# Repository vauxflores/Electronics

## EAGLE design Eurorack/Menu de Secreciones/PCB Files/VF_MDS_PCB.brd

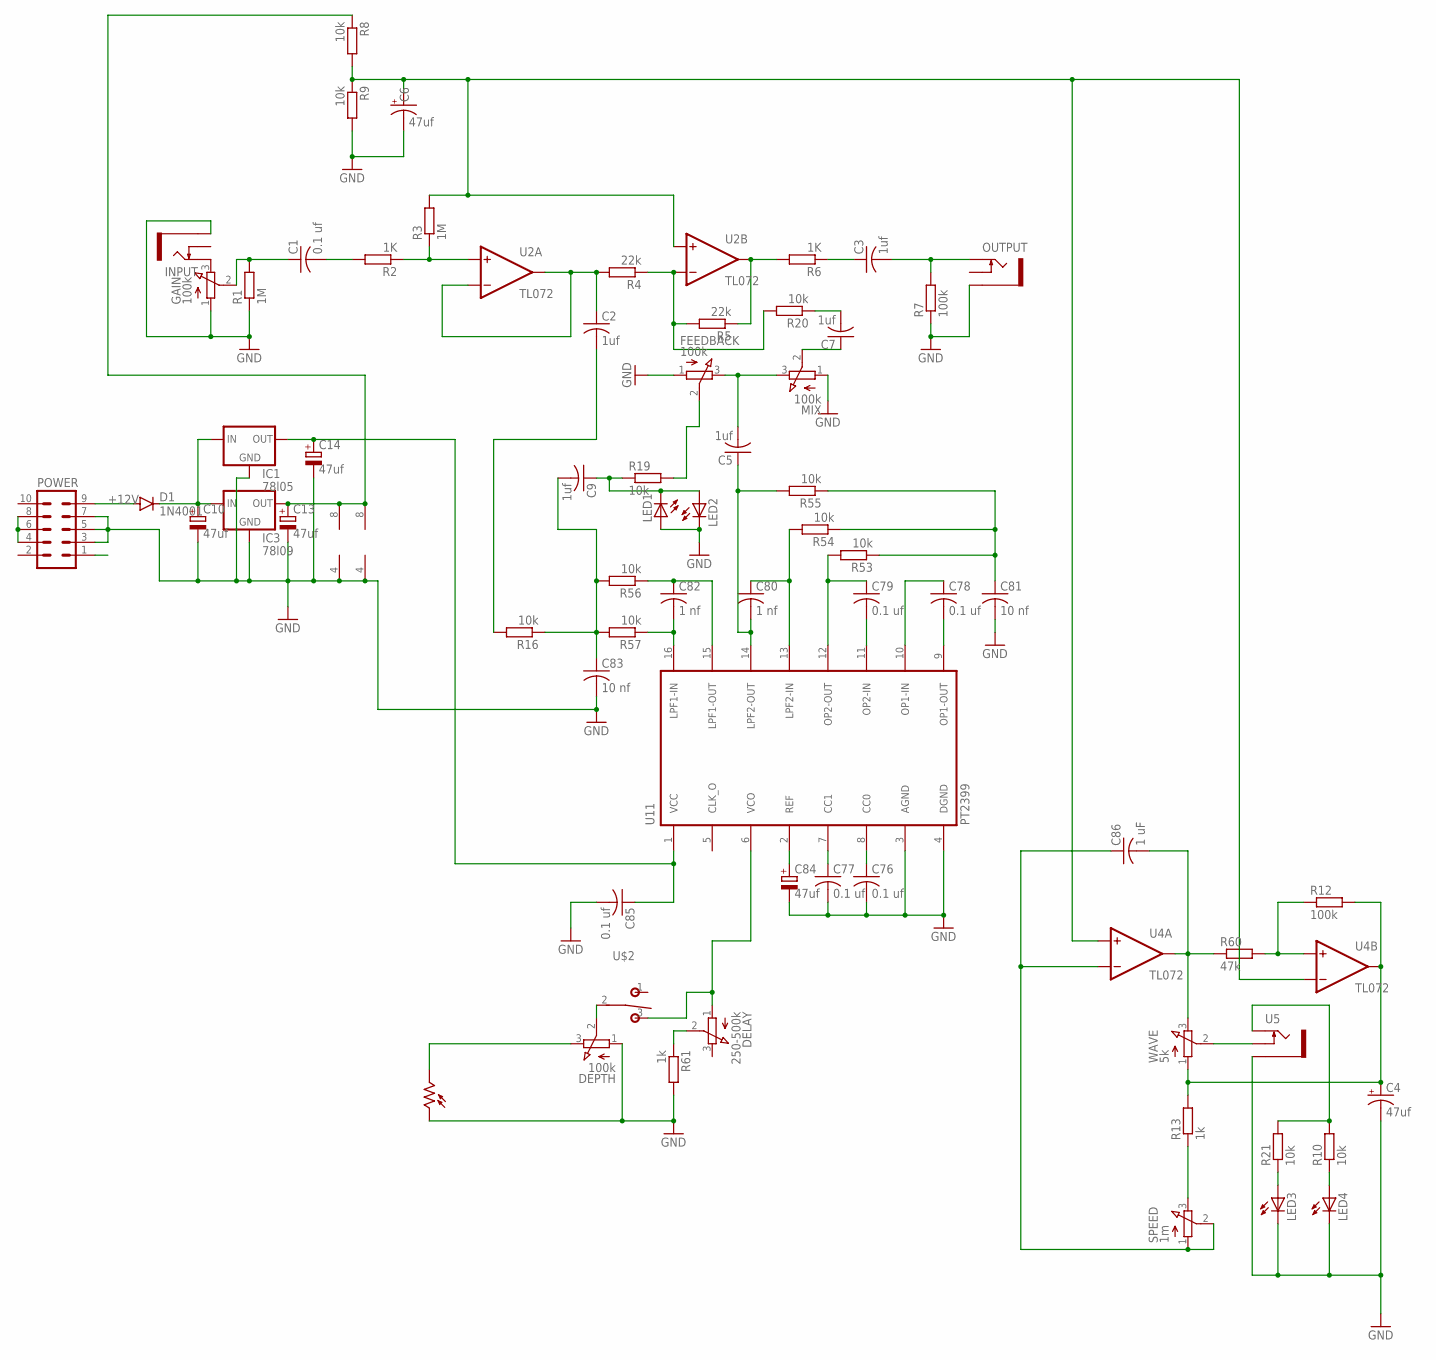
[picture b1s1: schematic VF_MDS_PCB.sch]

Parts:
C1, C76, C77, C78, C79, C85: 0.1 uf; C050-025X075
C2, C3, C5, C7, C9: 1uf; C050-025X075
C4, C6, C10, C13, C14, C84: 47uf; E2,5-6E
C80, C82: 1 nf; C050-025X075
C81, C83: 10 nf; C050-025X075
C86: 1 uF; C050-025X075
D1: 1N4001; DO41-10
DELAY: 250-500k; EVUFXL
DEPTH: 100k; EVUFXL
FEEDBACK: 100k; EVUFXL
GAIN: 100k; EVUFXL
IC1: 78l05; 78LXX
IC3: 78l09; 78LXX
INPUT: THONKICONNNEW; WQP-PJ301M-12_JACK
LED1, LED2: LED3MM
LED3, LED4: LED5MM
MIX: 100k; EVUFXL
OUTPUT: THONKICONNNEW; WQP-PJ301M-12_JACK
PH5: VT90N1; VT900
POWER: 10_PIN_HEADER; MA05-2
R1, R3: 1M; 7MM_RESISTOR
R2, R6: 1K; 7MM_RESISTOR
R4, R5: 22k; 7MM_RESISTOR
R7, R12: 100k; 7MM_RESISTOR
R8, R9, R10, R16, R19, R20, R21, R53, R54, R55, R56, R57: 10k; 7MM_RESISTOR
R13, R61: 1k; 7MM_RESISTOR
R60: 47k; 7MM_RESISTOR
SPEED: 1m; EVUFXL
U2, U4: TL072; DIL08-SML
U5: THONKICONNNEW; WQP-PJ301M-12_JACK
U11: PT2399; DIL16
U$2: T-80-T-SPDT-ON-OFF-ON; M9040P
WAVE: 5k; EVUFXL

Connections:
+12V: C10.+, D1.C, IC1.IN, IC3.IN
-12V: POWER.1
GND: C4.-, C6.-, C10.-, C13.-, C14.-, C76.2, C77.2, C81.2, C83.2, C84.-, C85.2, DEPTH.1 (A), FEEDBACK.1 (A), GAIN.1 (A), IC1.GND, IC3.GND, INPUT.P$3_SLEEVE (SLEEVE), LED1.A, LED2.K (C), LED3.K (C), LED4.K (C), MIX.1 (A), OUTPUT.P$3_SLEEVE (SLEEVE), PH5.1, POWER.3, POWER.5, POWER.7, R1.1, R7.1, R9.2, R61.2, U2.4 (V-), U4.4 (V-), U5.P$3_SLEEVE (SLEEVE), U11.3 (AGND), U11.4 (DGND)
GND2: POWER.4, POWER.6, POWER.8
unnamed: C1.1, GAIN.2 (S), R1.2
unnamed: C1.2, R2.2
unnamed: R2.1, R3.1, U2.3 (+IN)
unnamed: C2.1, R4.2, U2.1 (OUT), U2.2 (-IN)
unnamed: R4.1, R5.2, R20.2, U2.6 (-IN)
unnamed: R5.1, R6.2, U2.7 (OUT)
unnamed: C3.2, OUTPUT.P$1_TIP (TIP), R7.2
unnamed: C3.1, R6.1
unnamed: DELAY.2 (S), R61.1
unnamed: C6.+, R3.2, R8.2, R9.1, U2.5 (+IN), U4.3 (+IN), U4.6 (-IN)
unnamed: DEPTH.2 (S), U$2.2
unnamed: DEPTH.3 (E), PH5.2
unnamed: C86.2, R60.1, U4.1 (OUT), WAVE.3 (E)
unnamed: R12.1, R60.2, U4.5 (+IN)
unnamed: R13.1, SPEED.3 (E)
unnamed: C4.+, R12.2, R13.2, U4.7 (OUT), WAVE.1 (A)
unnamed: C86.1, SPEED.1 (A), SPEED.2 (S), U4.2 (-IN)
unnamed: GAIN.3 (E), INPUT.P$1_TIP (TIP)
unnamed: C5.2, FEEDBACK.3 (E), MIX.3 (E)
unnamed: C7.2, R20.1
unnamed: FEEDBACK.2 (S), R19.2
unnamed: C7.1, MIX.2 (S)
unnamed: C9.1, LED1.K (C), LED2.A, R19.1
unnamed: C9.2, C83.1, R16.1, R56.2, R57.2
unnamed: U5.P$2_SWITCH (SWITCH), WAVE.2 (S)
unnamed: R10.2, R21.2, U5.P$1_TIP (TIP)
unnamed: C2.2, R16.2
unnamed: LED3.A, R21.1
unnamed: C13.+, IC3.OUT, R8.1, U2.8 (V+), U4.8 (V+)
unnamed: D1.A, POWER.9
unnamed: LED4.A, R10.1
unnamed: C14.+, C85.1, IC1.OUT, U11.1 (VCC)
unnamed: DELAY.1 (A), U11.6 (VCO), U$2.3 (S)
unnamed: C76.1, U11.8 (CC0)
unnamed: C77.1, U11.7 (CC1)
unnamed: C78.2, U11.9 (OP1-OUT)
unnamed: C78.1, U11.10 (OP1-IN)
unnamed: C79.2, U11.11 (OP2-IN)
unnamed: C79.1, R53.2, U11.12 (OP2-OUT)
unnamed: C5.1, C80.2, R55.2, U11.14 (LPF2-OUT)
unnamed: C80.1, R54.2, U11.13 (LPF2-IN)
unnamed: C81.1, R53.1, R54.1, R55.1
unnamed: C82.2, R57.1, U11.16 (LPF1-IN)
unnamed: C82.1, R56.1, U11.15 (LPF1-OUT)
unnamed: C84.+, U11.2 (REF)

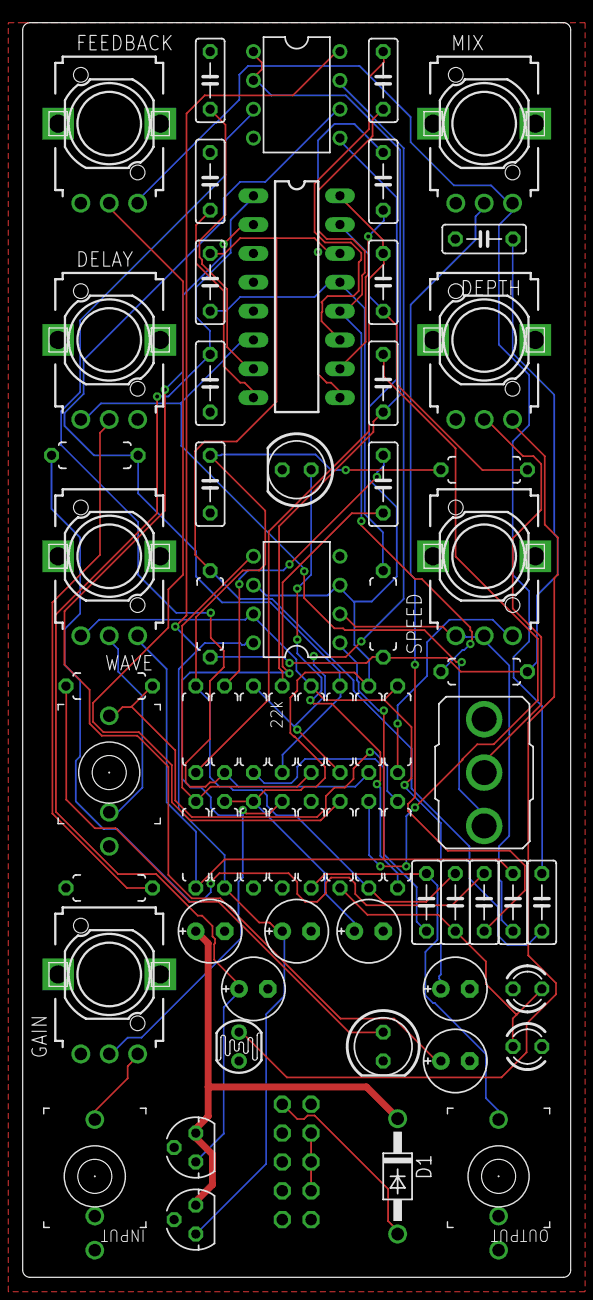
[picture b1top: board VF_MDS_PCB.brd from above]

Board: 2 copper layers, 48.3 x 110.5 mm, 69 parts (1 on the bottom side), 48 nets.

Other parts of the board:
U$1: EURO_PCB_10HP

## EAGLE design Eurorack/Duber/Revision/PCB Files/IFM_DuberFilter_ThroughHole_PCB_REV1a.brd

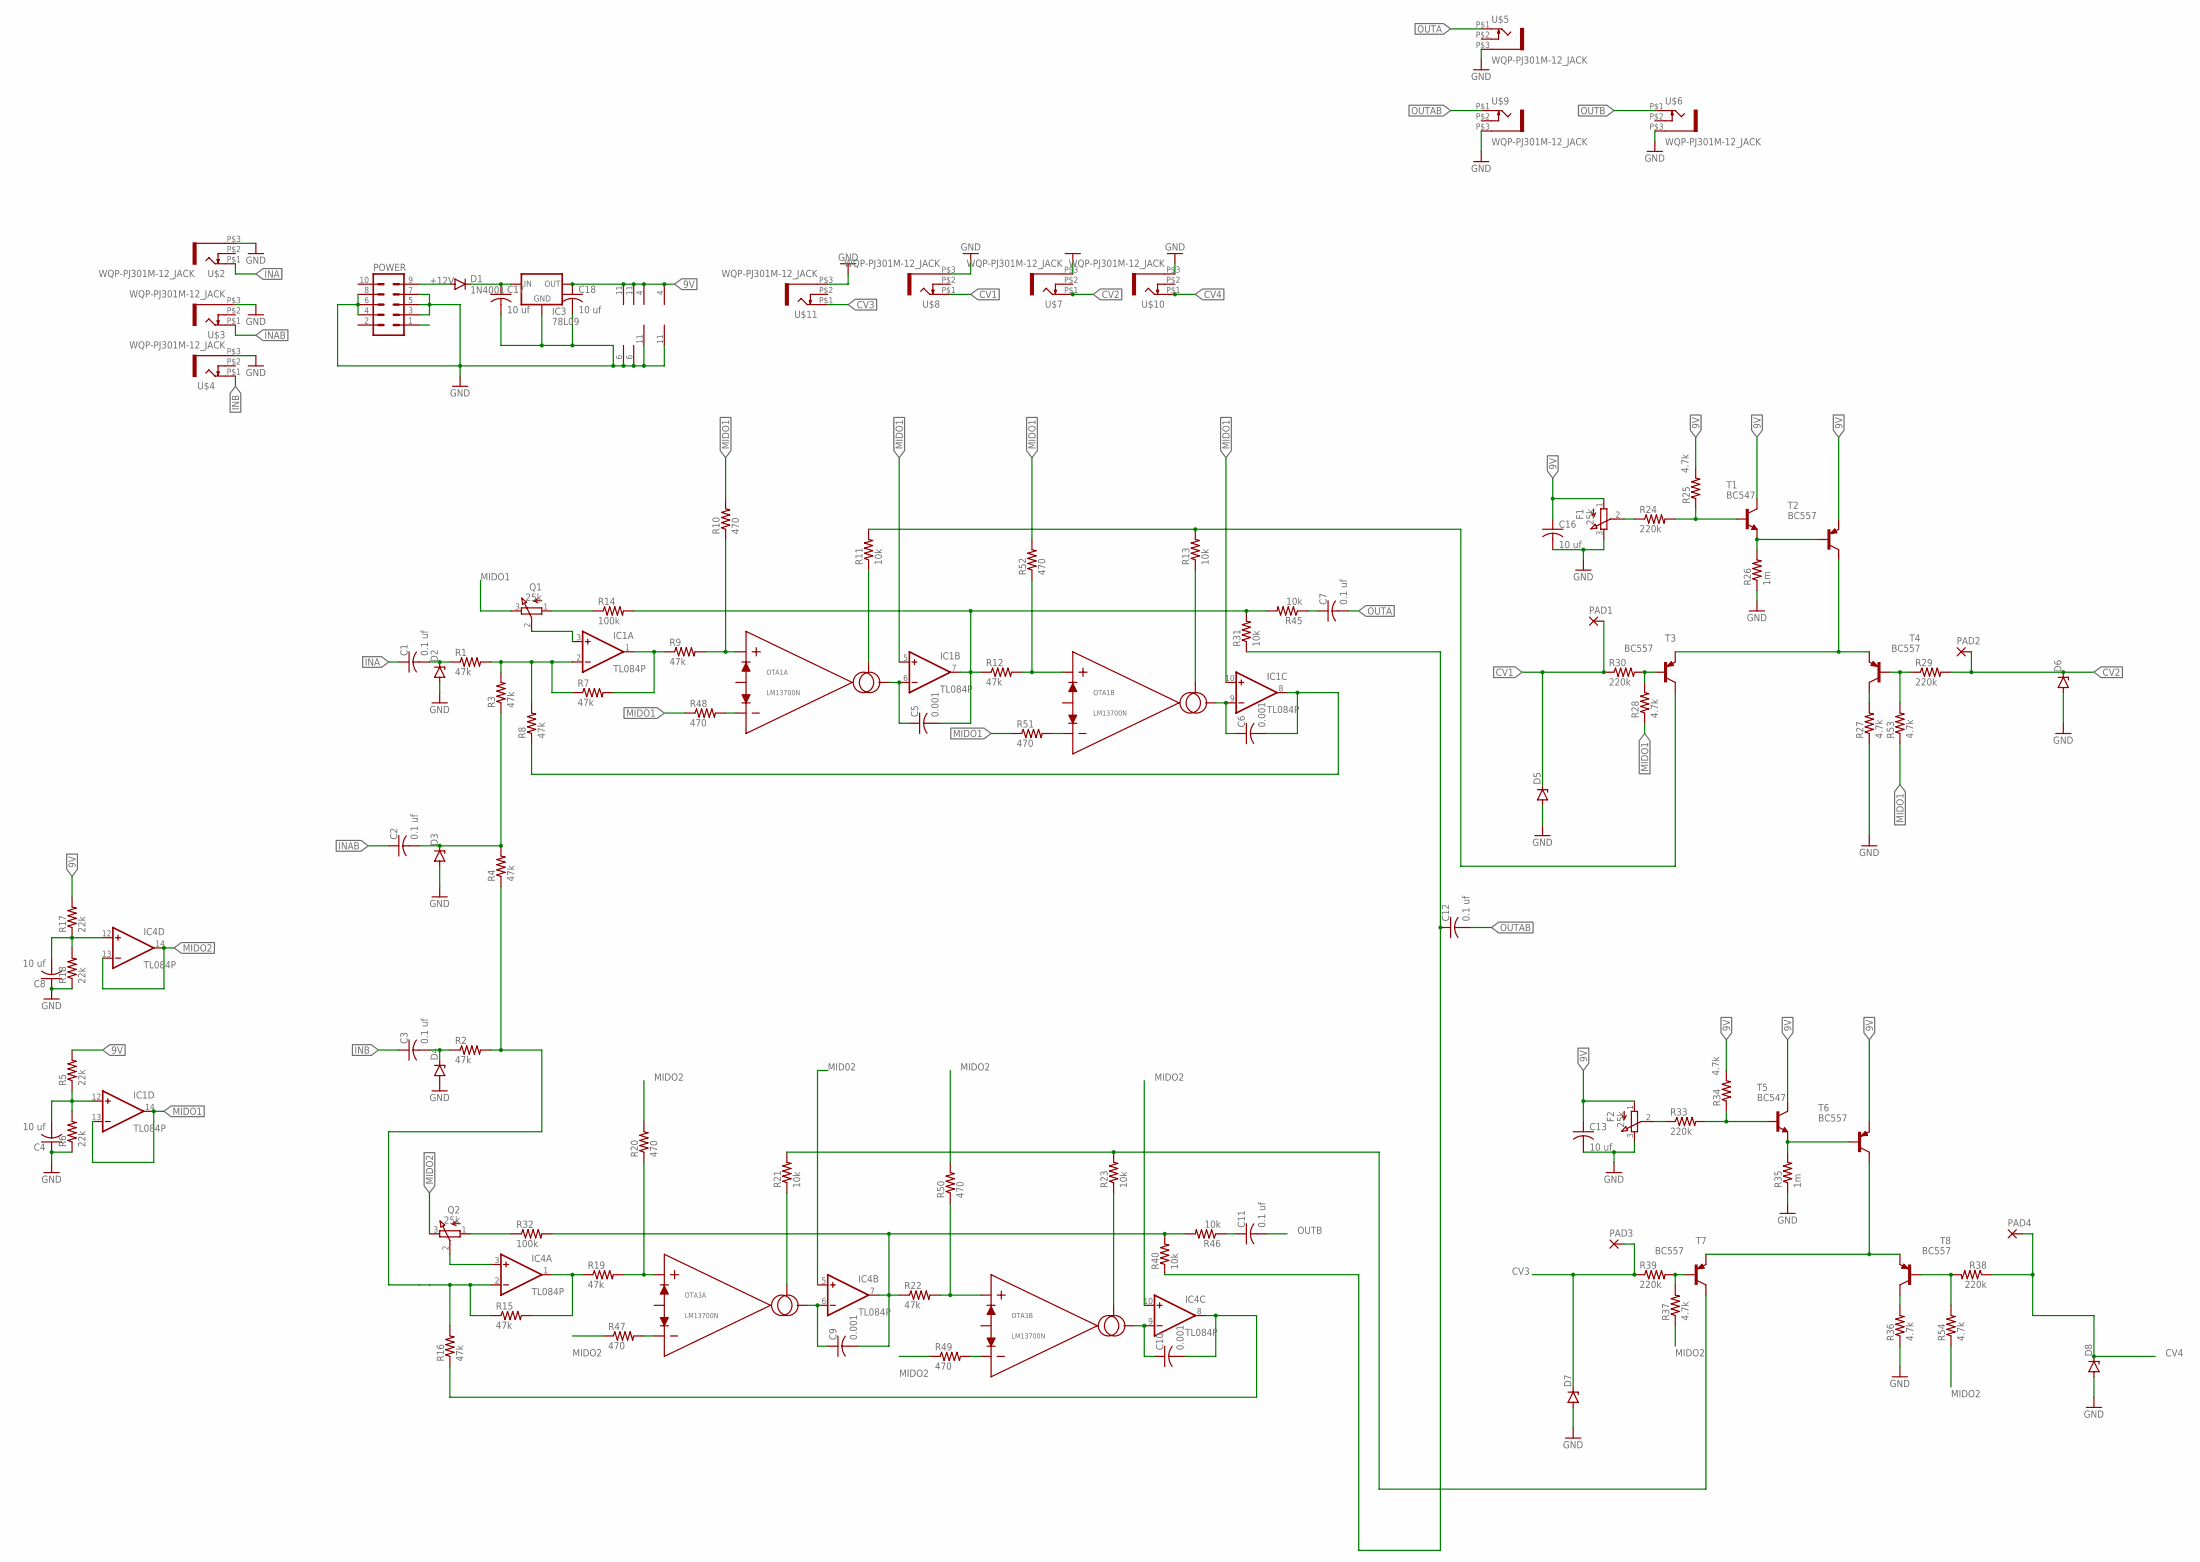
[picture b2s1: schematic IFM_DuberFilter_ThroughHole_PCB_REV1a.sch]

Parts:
C1, C2, C3, C7, C11, C12: 0.1 uf; C050-030X075
C4, C8, C13, C16, C17, C18: 10 uf; C050-030X075
C5, C6, C9, C10: 0.001; C050-030X075
D1: 1N4001; DO41-10
D2, D3, D4, D5, D6, D7, D8: ZENER-DIODEDO34-7; DO34Z7
F1, F2: 25k; EVUFXL
IC1, IC4: TL084P; DIL14
IC3: 78L09; 78LXX
OTA1, OTA3: LM13700N; DIP16
PAD1, PAD2, PAD3, PAD4: SMD2; SMD1,27-2,54
POWER: 10_PIN_HEADER; MA05-2
Q1, Q2: 25k; EVUFXL
R1, R2, R3, R4, R7, R8, R9, R12, R15, R16, R19, R22: 47k; 0204/7
R5, R6, R17, R18: 22k; 0204/7
R10, R20, R47, R48, R49, R50, R51, R52: 470; 0204/7
R11, R13, R21, R23, R31, R40, R45, R46: 10k; 0204/7
R14, R32: 100k; 0204/7
R24, R29, R30, R33, R38, R39: 220k; 0204/7
R25, R27, R28, R34, R36, R37, R53, R54: 4.7k; 0204/7
R26, R35: 1m; 0204/7
T1, T5: BC547; TO92
T2, T3, T4, T6, T7, T8: BC557; TO92-EBC
U$2, U$3, U$4, U$5, U$6, U$7, U$8, U$9, U$10, U$11: WQP-PJ301M-12_JACK

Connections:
9V: C13.1, C16.1, C18.1, F1.1 (A), F2.1 (A), IC1.4 (V+), IC3.OUT, IC4.4 (V+), OTA1.11 (VCC), OTA3.11 (VCC), R5.2, R17.2, R25.2, R34.2, T1.3 (C), T2.E, T5.3 (C), T6.E
+12V: C17.1, D1.C, IC3.IN
-12V: POWER.1
CV1: D5.C, PAD1.1, R30.1, U$8.P$1 (2)
CV2: D6.C, PAD2.1, R29.2, U$7.P$1 (2)
CV3: D7.C, PAD3.1, R39.1, U$11.P$1 (2)
CV4: D8.C, PAD4.1, R38.1, U$10.P$1 (2)
GND: C4.1, C8.1, C13.2, C16.2, C17.2, C18.2, D2.A, D3.A, D4.A, D5.A, D6.A, D7.A, D8.A, F1.3 (E), F2.3 (E), IC1.11 (V-), IC3.GND, IC4.11 (V-), OTA1.6 (VEE), OTA3.6 (VEE), POWER.3, POWER.4, POWER.5, POWER.6, POWER.7, POWER.8, R6.1, R18.1, R26.1, R27.1, R35.1, R36.1, U$2.P$3 (1), U$3.P$3 (1), U$4.P$3 (1), U$5.P$3 (1), U$6.P$3 (1), U$7.P$3 (1), U$8.P$3 (1), U$9.P$3 (1), U$10.P$3 (1), U$11.P$3 (1)
INA: C1.1, U$2.P$1 (2)
INAB: C2.1, U$3.P$1 (2)
INB: C3.1, U$4.P$1 (2)
MID02: IC4.5 (+IN)
MIDO1: IC1.5 (+IN), IC1.10 (+IN), IC1.13 (-IN), IC1.14 (OUT), Q1.3 (E), R10.2, R28.1, R48.1, R51.1, R52.2, R53.1
MIDO2: IC4.10 (+IN), IC4.13 (-IN), IC4.14 (OUT), Q2.3 (E), R20.2, R37.1, R47.1, R49.1, R50.2, R54.1
unnamed: C3.2, D4.C, R2.1
unnamed: C1.2, D2.C, R1.1
unnamed: C2.2, D3.C, R3.1, R4.2
unnamed: IC4.2 (-IN), R2.2, R4.1, R15.1, R16.2
unnamed: IC1.2 (-IN), R1.2, R3.2, R7.1, R8.2
unnamed: OTA1.16 (IABC), R13.1
unnamed: C4.2, IC1.12 (+IN), R5.1, R6.2
unnamed: Q1.1 (A), R14.1
unnamed: OTA1.13 (IN-), R51.2
unnamed: IC4.1 (OUT), R15.2, R19.1
unnamed: IC1.1 (OUT), R7.2, R9.1
unnamed: OTA1.3 (IN+), R9.2, R10.1
unnamed: C5.1, IC1.6 (-IN), OTA1.5 (IOUT)
unnamed: OTA1.1 (IABC), R11.1
unnamed: C5.2, IC1.7 (OUT), R12.1, R14.2, R31.2, R45.2
unnamed: R29.1, R53.2, T4.B
unnamed: R11.2, R13.2, T3.C
unnamed: C6.1, IC1.9 (-IN), OTA1.12 (IOUT)
unnamed: C6.2, IC1.8 (OUT), R8.1
unnamed: IC1.3 (+IN), Q1.2 (S)
unnamed: F1.2 (S), R24.1
unnamed: OTA1.14 (IN+), R12.2, R52.1
unnamed: OTA3.3 (IN+), R19.2, R20.1
unnamed: C8.2, IC4.12 (+IN), R17.1, R18.2
unnamed: C9.1, IC4.6 (-IN), OTA3.5 (IOUT)
unnamed: OTA3.1 (IABC), R21.1
unnamed: C9.2, IC4.7 (OUT), R22.1, R32.2, R40.2, R46.2
unnamed: OTA3.16 (IABC), R23.1
unnamed: R21.2, R23.2, T7.C
unnamed: Q2.1 (A), R32.1
unnamed: C10.1, IC4.9 (-IN), OTA3.12 (IOUT)
unnamed: C10.2, IC4.8 (OUT), R16.1
unnamed: D1.A, POWER.9
unnamed: IC4.3 (+IN), Q2.2 (S)
unnamed: OTA1.4 (IN-), R48.2
unnamed: R33.2, R34.1, T5.2 (B)
unnamed: R24.2, R25.1, T1.2 (B)
unnamed: R26.2, T1.1 (E), T2.B
unnamed: T2.C, T3.E, T4.E
unnamed: R35.2, T5.1 (E), T6.B
unnamed: R27.2, T4.C
unnamed: C12.1, R31.1, R40.1
unnamed: R28.2, R30.2, T3.B
unnamed: F2.2 (S), R33.1
unnamed: C11.1, R46.1
unnamed: T6.C, T7.E, T8.E
unnamed: R36.2, T8.C
unnamed: R38.2, R54.2, T8.B
unnamed: R37.2, R39.2, T7.B
unnamed: OTA3.4 (IN-), R47.2
unnamed: OTA3.13 (IN-), R49.2
unnamed: OTA3.14 (IN+), R22.2, R50.1
unnamed: C7.1, R45.1
OUTA: C7.2, U$5.P$1 (2)
OUTAB: C12.2, U$9.P$1 (2)
OUTB: C11.2, U$6.P$1 (2)

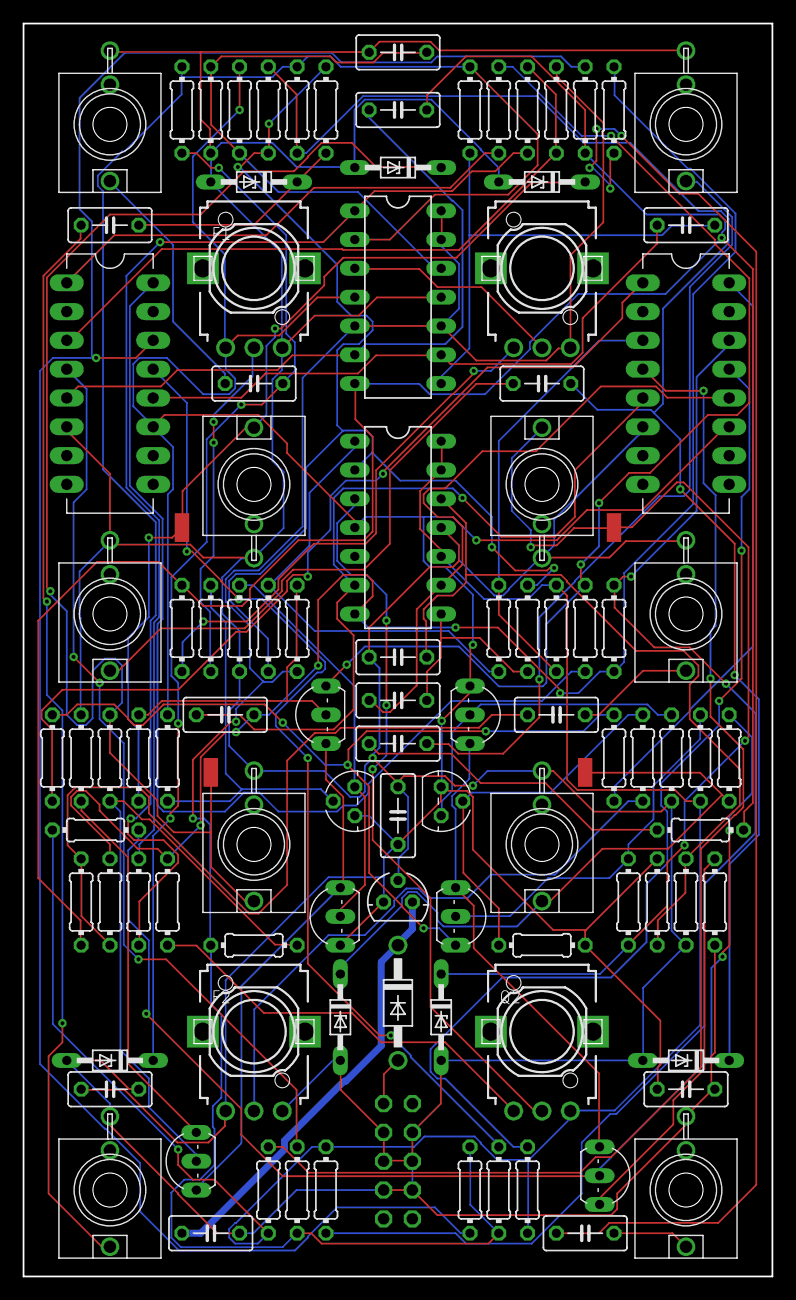
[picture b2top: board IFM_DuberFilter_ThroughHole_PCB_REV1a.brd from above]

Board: 2 copper layers, 66.0 x 110.5 mm, 106 parts (1 on the bottom side), 68 nets.

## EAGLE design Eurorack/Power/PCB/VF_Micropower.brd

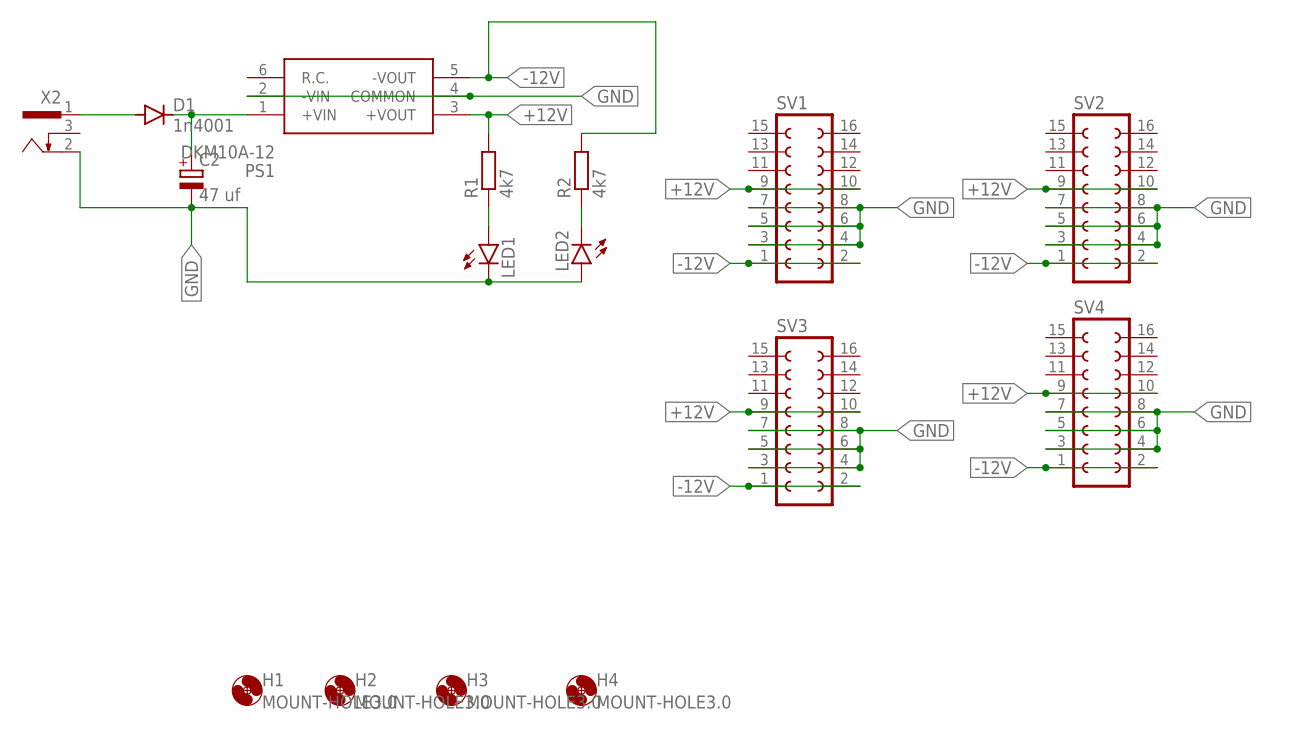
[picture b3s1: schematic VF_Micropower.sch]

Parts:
C2: 47 uf; E2,5-6E
D1: 1n4001; DO41-10
H1, H2, H3, H4: MOUNT-HOLE3.0; 3,0
LED1, LED2: LED3MM
PS1: DKM10A-12; SKM10B05
R1, R2: 4k7; 0207/10
SV1, SV2, SV3, SV4: FE08-2
X2: SCD-014A; SCD-014-A

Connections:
+12V: PS1.3 (+VOUT), R1.2, SV1.9, SV1.10, SV2.9, SV2.10, SV3.9, SV3.10, SV4.9, SV4.10
-12V: PS1.5 (-VOUT), R2.2, SV1.1, SV1.2, SV2.1, SV2.2, SV3.1, SV3.2, SV4.1, SV4.2
GND: C2.-, LED1.K (C), LED2.A, PS1.2 (-VIN), PS1.4 (COMMON), SV1.3, SV1.4, SV1.5, SV1.6, SV1.7, SV1.8, SV2.3, SV2.4, SV2.5, SV2.6, SV2.7, SV2.8, SV3.3, SV3.4, SV3.5, SV3.6, SV3.7, SV3.8, SV4.3, SV4.4, SV4.5, SV4.6, SV4.7, SV4.8, X2.2
unnamed: C2.+, D1.C, PS1.1 (+VIN)
unnamed: D1.A, X2.1
unnamed: LED1.A, R1.1
unnamed: LED2.K (C), R2.1

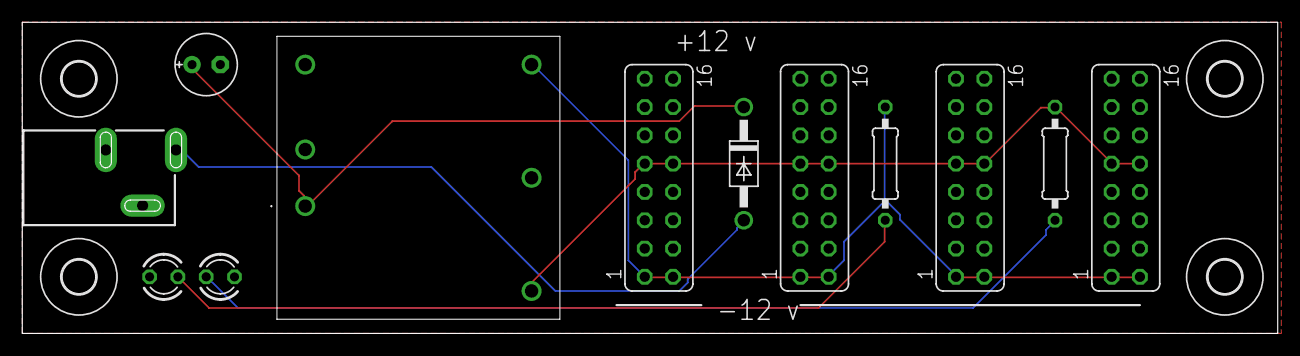
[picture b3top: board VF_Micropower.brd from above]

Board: 2 copper layers, 112.7 x 27.9 mm, 16 parts (0 on the bottom side), 7 nets.

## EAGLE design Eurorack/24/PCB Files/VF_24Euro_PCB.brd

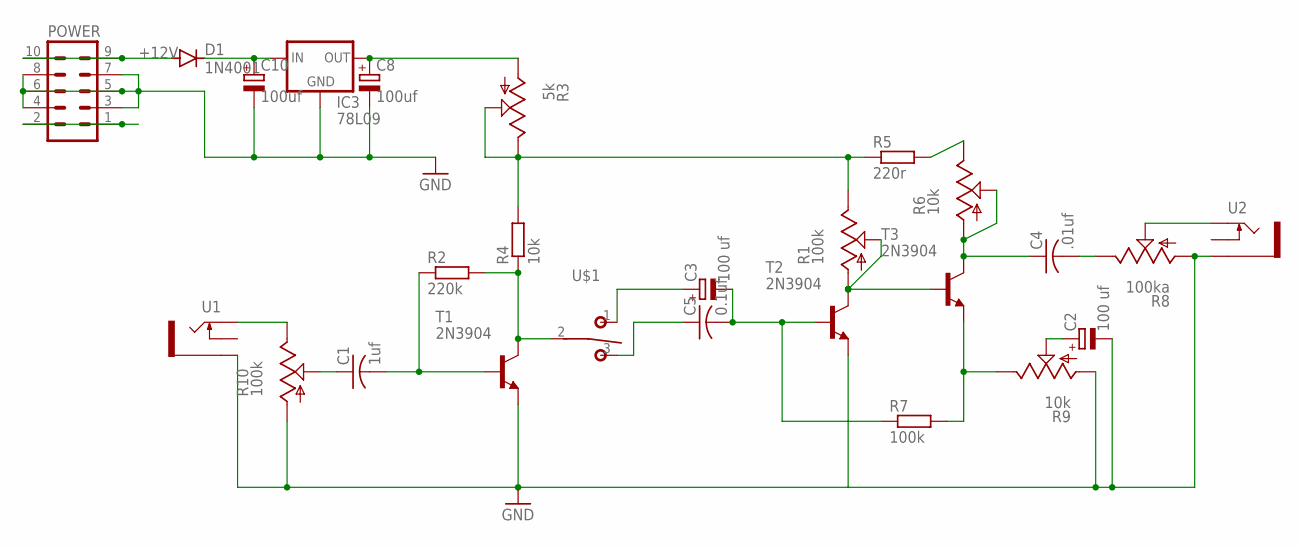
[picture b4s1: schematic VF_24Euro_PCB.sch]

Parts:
C1: 1uf; C050-025X075
C2, C3: 100 uf; E2,5-7
C4: .01uf; C050-025X075
C5: 0.1uf; C050-025X075
C8, C10: 100uf; E2,5-7
D1: 1N4001; DO41-10
IC3: 78L09; 78LXX
POWER: 10_PIN_HEADER; MA05-2
R1, R10: 100k; 9MM_SNAP-IN_POT
R2: 220k; 7MM_RESISTOR
R3: 5k; 9MM_SNAP-IN_POT
R4: 10k; 7MM_RESISTOR
R5: 220r; 7MM_RESISTOR
R6, R9: 10k; 9MM_SNAP-IN_POT
R7: 100k; 7MM_RESISTOR
R8: 100ka; 9MM_SNAP-IN_POT
T1, T2, T3: 2N3904; TO92
U1, U2: THONKICONNNEW; WQP-PJ301M-12_JACK
U$1: T-80-T-SPDT-ON-OFF-ON; M9040P

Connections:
+12V: C10.+, D1.C, IC3.IN
-12V: POWER.1, POWER.2
GND: C2.-, C8.-, C10.-, IC3.GND, POWER.3, POWER.4, POWER.5, POWER.6, POWER.7, POWER.8, R8.1 (A), R9.1 (A), R10.1 (A), T1.3 (E), T2.3 (E), U1.P$3_SLEEVE (SLEEVE), U2.P$3_SLEEVE (SLEEVE)
unnamed: C1.2, R2.1, T1.2 (B)
unnamed: R2.2, R4.1, T1.1 (C), U$1.2
unnamed: R1.3 (E), R3.2 (S), R3.3 (E), R4.2, R5.1
unnamed: C5.1, U$1.3 (S)
unnamed: C3.+, U$1.1 (O)
unnamed: C3.-, C5.2, R7.1, T2.2 (B)
unnamed: R1.1 (A), R1.2 (S), T2.1 (C), T3.2 (B)
unnamed: R5.2, R6.3 (E)
unnamed: C4.1, R6.1 (A), R6.2 (S), T3.1 (C)
unnamed: C4.2, R8.3 (E)
unnamed: C2.+, R9.2 (S)
unnamed: R10.3 (E), U1.P$1_TIP (TIP)
unnamed: C1.1, R10.2 (S)
unnamed: R8.2 (S), U2.P$1_TIP (TIP)
unnamed: D1.A, POWER.9, POWER.10
unnamed: R7.2, R9.3 (E), T3.3 (E)
unnamed: C8.+, IC3.OUT, R3.1 (A)

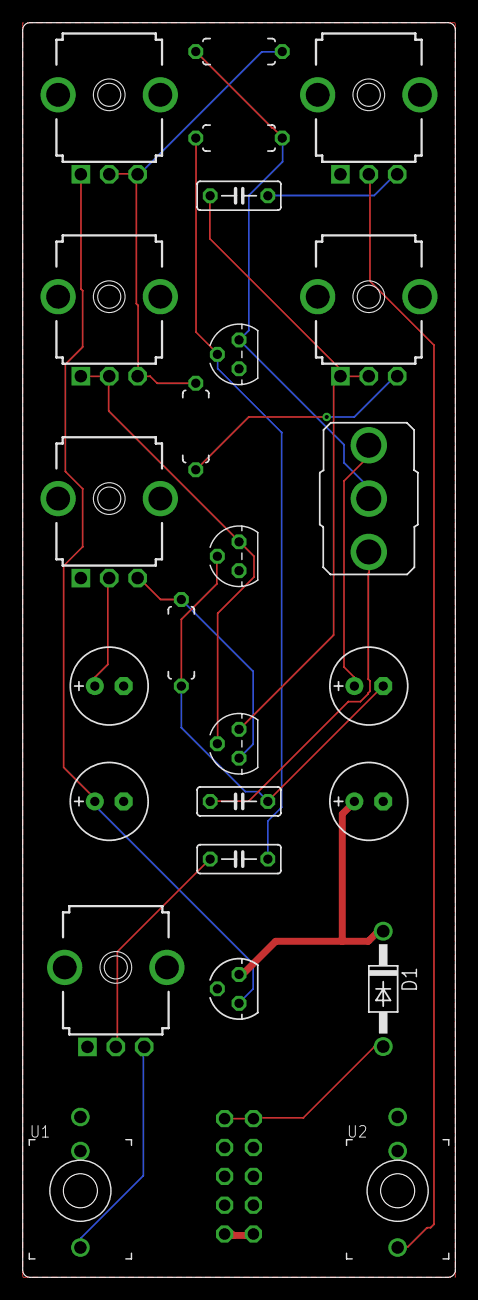
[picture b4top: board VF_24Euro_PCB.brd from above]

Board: 2 copper layers, 38.1 x 110.5 mm, 27 parts (1 on the bottom side), 20 nets.

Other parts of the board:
U$2: EURO_PCB_8HP

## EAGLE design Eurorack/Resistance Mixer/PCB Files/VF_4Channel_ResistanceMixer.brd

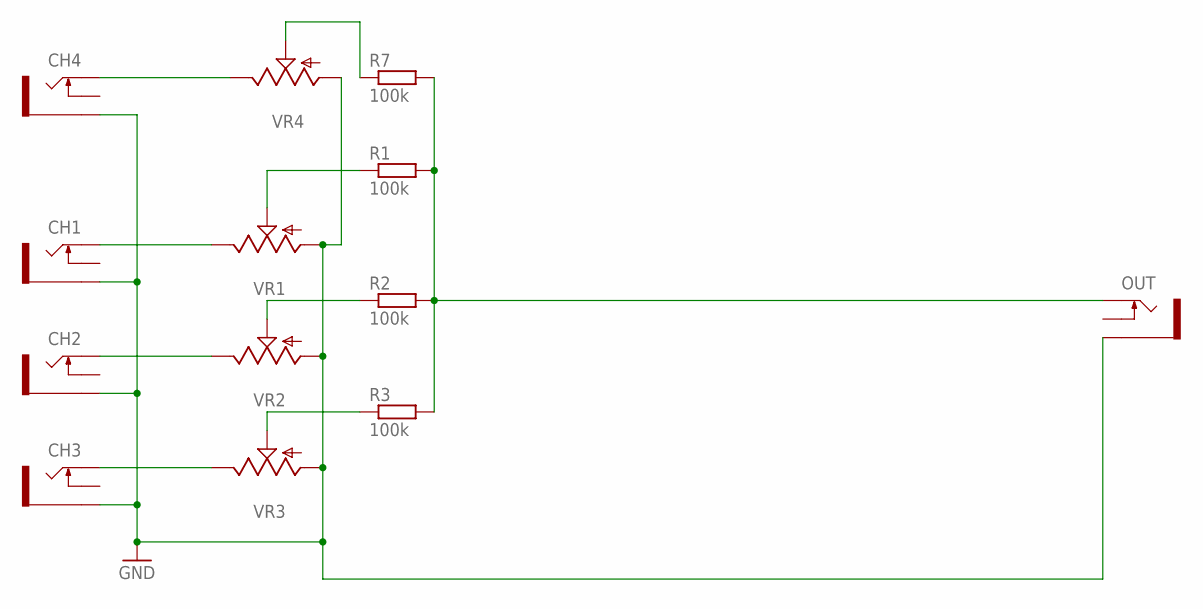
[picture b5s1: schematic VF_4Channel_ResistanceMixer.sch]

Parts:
CH1, CH2, CH3, CH4: THONKICONNNEW; WQP-PJ301M-12_JACK
OUT: THONKICONNNEW; WQP-PJ301M-12_JACK
R1, R2, R3, R7: 100k; 7MM_RESISTOR
VR1, VR2, VR3, VR4: 9MM_SNAP-IN_POT_; 9MM_SNAP-IN_POT

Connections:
GND: CH1.P$3_SLEEVE (SLEEVE), CH2.P$3_SLEEVE (SLEEVE), CH3.P$3_SLEEVE (SLEEVE), CH4.P$3_SLEEVE (SLEEVE), OUT.P$3_SLEEVE (SLEEVE), VR1.1 (A), VR2.1 (A), VR3.1 (A), VR4.1 (A)
unnamed: CH3.P$1_TIP (TIP), VR3.3 (E)
unnamed: CH2.P$1_TIP (TIP), VR2.3 (E)
unnamed: CH1.P$1_TIP (TIP), VR1.3 (E)
unnamed: R3.1, VR3.2 (S)
unnamed: R2.1, VR2.2 (S)
unnamed: R1.1, VR1.2 (S)
unnamed: CH4.P$1_TIP (TIP), VR4.3 (E)
unnamed: OUT.P$1_TIP (TIP), R1.2, R2.2, R3.2, R7.2
unnamed: R7.1, VR4.2 (S)

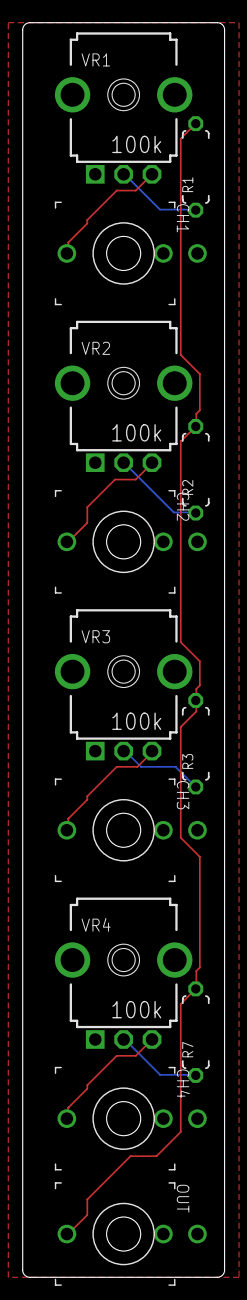
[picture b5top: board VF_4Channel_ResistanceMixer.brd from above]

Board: 2 copper layers, 17.8 x 110.5 mm, 14 parts (0 on the bottom side), 10 nets.

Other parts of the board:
U$2: EURO_PCB_4HP

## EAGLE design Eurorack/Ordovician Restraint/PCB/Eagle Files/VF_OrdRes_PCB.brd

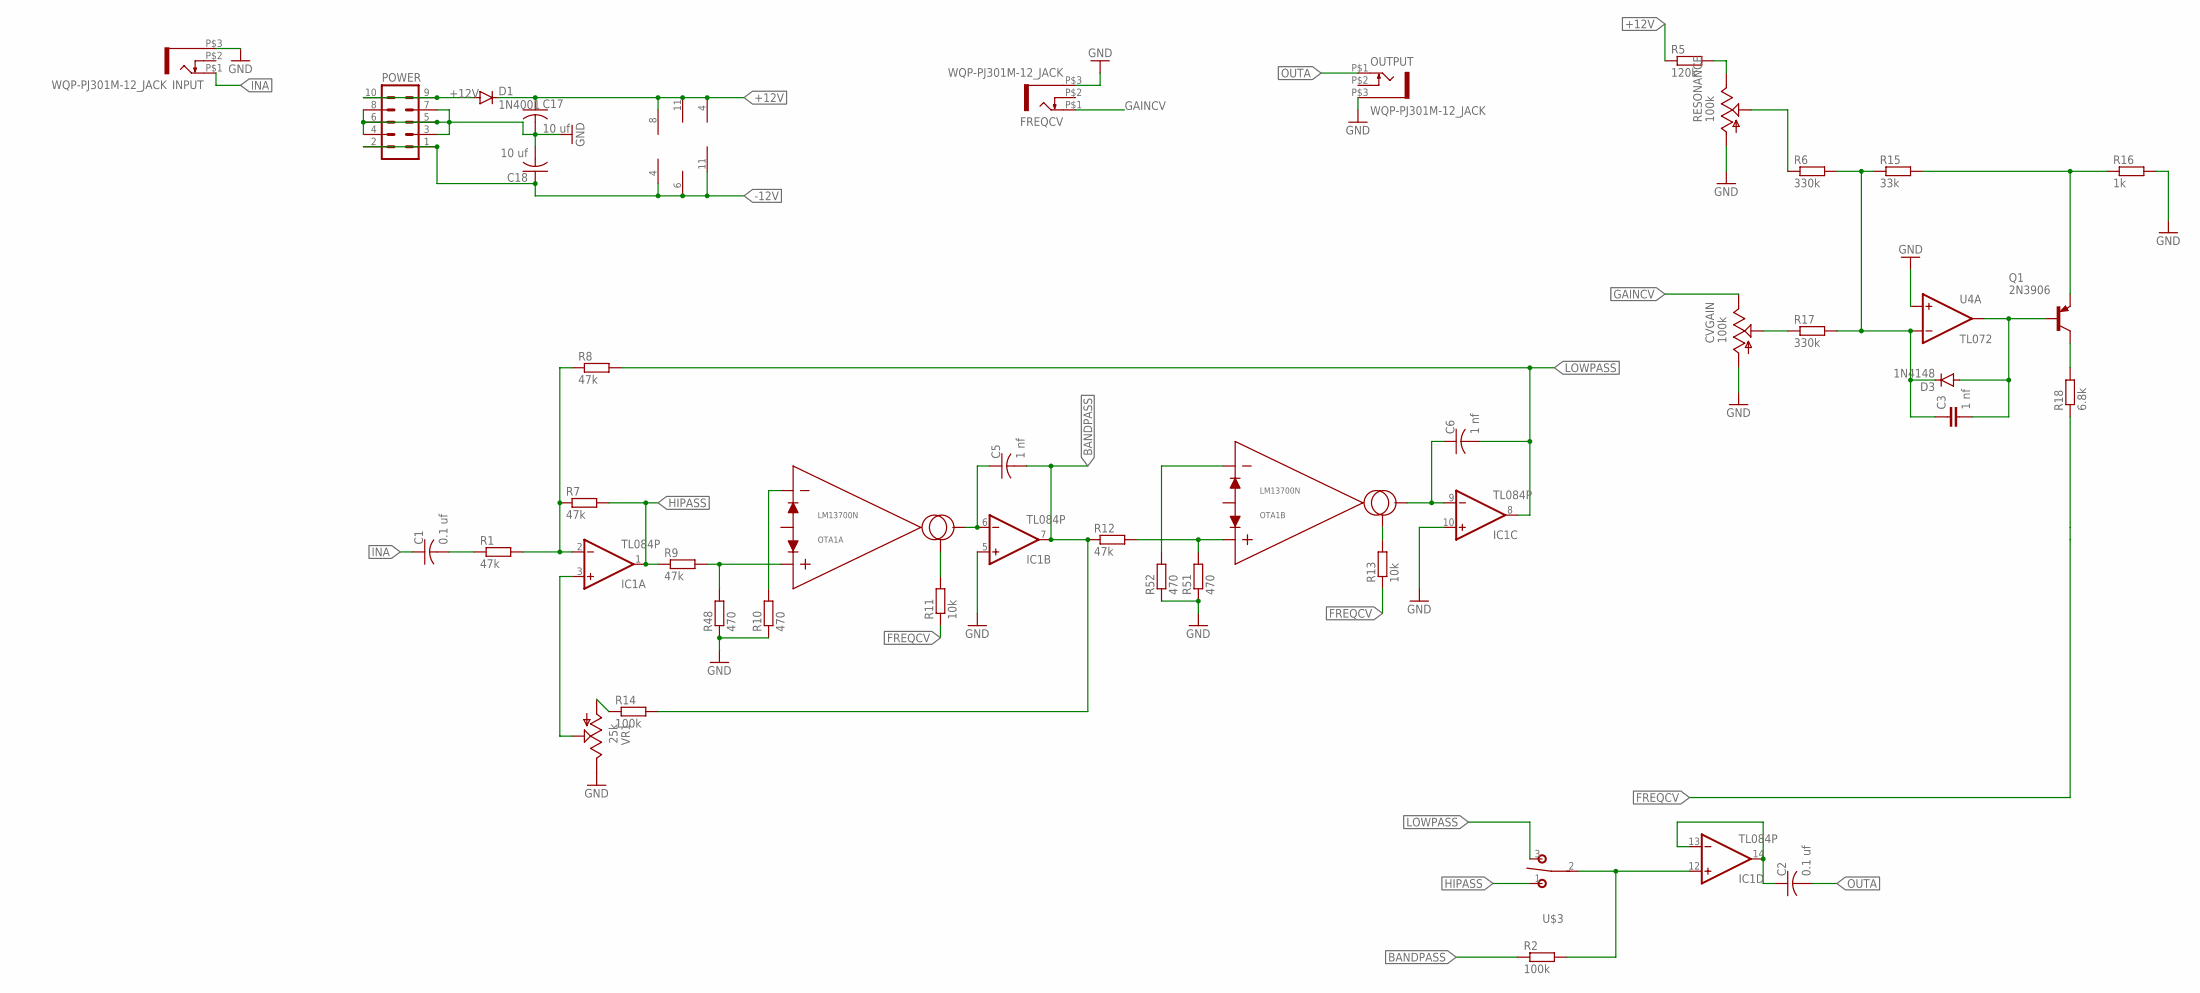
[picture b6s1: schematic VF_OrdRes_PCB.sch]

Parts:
C1, C2: 0.1 uf; C050-030X075
C3: 1 nf; C050-025X075
C5, C6: 1 nf; C050-030X075
C17, C18: 10 uf; C050-030X075
CVGAIN: 100k; 9MM_SNAP-IN_POT
D1: 1N4001; DO41-10
D3: 1N4148; DO35-7
FREQCV: WQP-PJ301M-12_JACK
IC1: TL084P; DIL14
INPUT: WQP-PJ301M-12_JACK
OTA1: LM13700N; DIP16
OUTPUT: WQP-PJ301M-12_JACK
POWER: 10_PIN_HEADER; MA05-2
Q1: 2N3906; TO92
R1, R7, R8, R9, R12: 47k; 7MM_RESISTOR
R2, R14: 100k; 7MM_RESISTOR
R5: 120k; 7MM_RESISTOR
R6, R17: 330k; 7MM_RESISTOR
R10, R48, R51, R52: 470; 7MM_RESISTOR
R11, R13: 10k; 7MM_RESISTOR
R15: 33k; 7MM_RESISTOR
R16: 1k; 7MM_RESISTOR
R18: 6.8k; 7MM_RESISTOR
RESONANCE: 100k; 9MM_SNAP-IN_POT
U4: TL072; DIL08-SML
U$3: T-80-T-SPDT-ON-OFF-ON; M9040P
VR1: 25k; 9MM_SNAP-IN_POT

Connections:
+12V: C17.1, D1.C, IC1.4 (V+), OTA1.11 (VCC), R5.1, U4.8 (V+)
-12V: C18.1, IC1.11 (V-), OTA1.6 (VEE), POWER.1, POWER.2, U4.4 (V-)
BANDPASS: C5.2, IC1.7 (OUT), R2.1, R12.1, R14.2
FREQCV: R11.1, R13.1, R18.1
GAINCV: CVGAIN.3 (E), FREQCV.P$1 (2)
GND: C17.2, C18.2, CVGAIN.1 (A), FREQCV.P$3 (1), IC1.5 (+IN), IC1.10 (+IN), INPUT.P$3 (1), OUTPUT.P$3 (1), POWER.3, POWER.4, POWER.5, POWER.6, POWER.7, POWER.8, R10.1, R16.2, R48.1, R51.1, R52.1, RESONANCE.1 (A), U4.3 (+IN), VR1.3 (E)
HIPASS: IC1.1 (OUT), R7.2, R9.1, U$3.1 (O)
INA: C1.1, INPUT.P$1 (2)
LOWPASS: C6.2, IC1.8 (OUT), R8.2, U$3.3 (S)
unnamed: IC1.12 (+IN), R2.2, U$3.2
unnamed: C1.2, R1.1
unnamed: R5.2, RESONANCE.3 (E)
unnamed: C2.1, IC1.13 (-IN), IC1.14 (OUT)
unnamed: IC1.2 (-IN), R1.2, R7.1, R8.1
unnamed: IC1.3 (+IN), VR1.2 (S)
unnamed: R14.1, VR1.1 (A)
unnamed: OTA1.3 (IN+), R9.2, R48.2
unnamed: OTA1.4 (IN-), R10.2
unnamed: C5.1, IC1.6 (-IN), OTA1.5 (IOUT)
unnamed: OTA1.1 (IABC), R11.2
unnamed: OTA1.14 (IN+), R12.2, R51.2
unnamed: OTA1.13 (IN-), R52.2
unnamed: OTA1.16 (IABC), R13.2
unnamed: C6.1, IC1.9 (-IN), OTA1.12 (IOUT)
unnamed: C3.1, D3.C, R6.2, R15.1, R17.2, U4.2 (-IN)
unnamed: Q1.3 (E), R15.2, R16.1
unnamed: R6.1, RESONANCE.2 (S)
unnamed: CVGAIN.2 (S), R17.1
unnamed: C3.2, D3.A, Q1.2 (B), U4.1 (OUT)
unnamed: Q1.1 (C), R18.2
unnamed: D1.A, POWER.9, POWER.10
OUTA: C2.2, OUTPUT.P$1 (2)

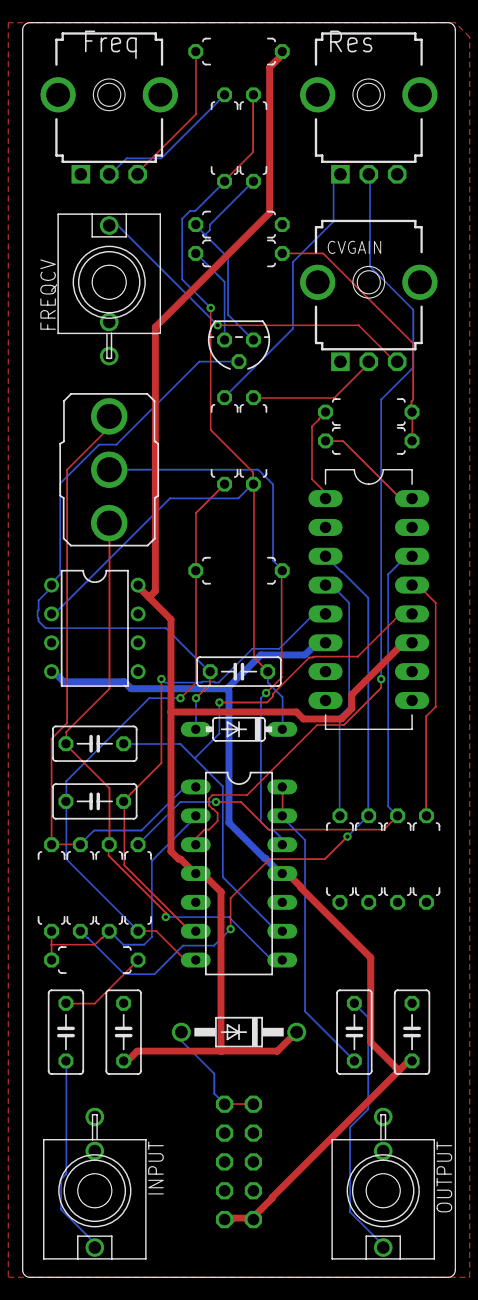
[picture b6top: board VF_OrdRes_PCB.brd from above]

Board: 2 copper layers, 38.1 x 110.5 mm, 41 parts (1 on the bottom side), 32 nets.

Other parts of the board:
U$1: EURO_PCB_8HP

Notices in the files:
parts and their libraries:
OTAs: Copyright © David H. Christensen, 2017.
princeton-tech: Copyright (C) 2010, Bob Starr
